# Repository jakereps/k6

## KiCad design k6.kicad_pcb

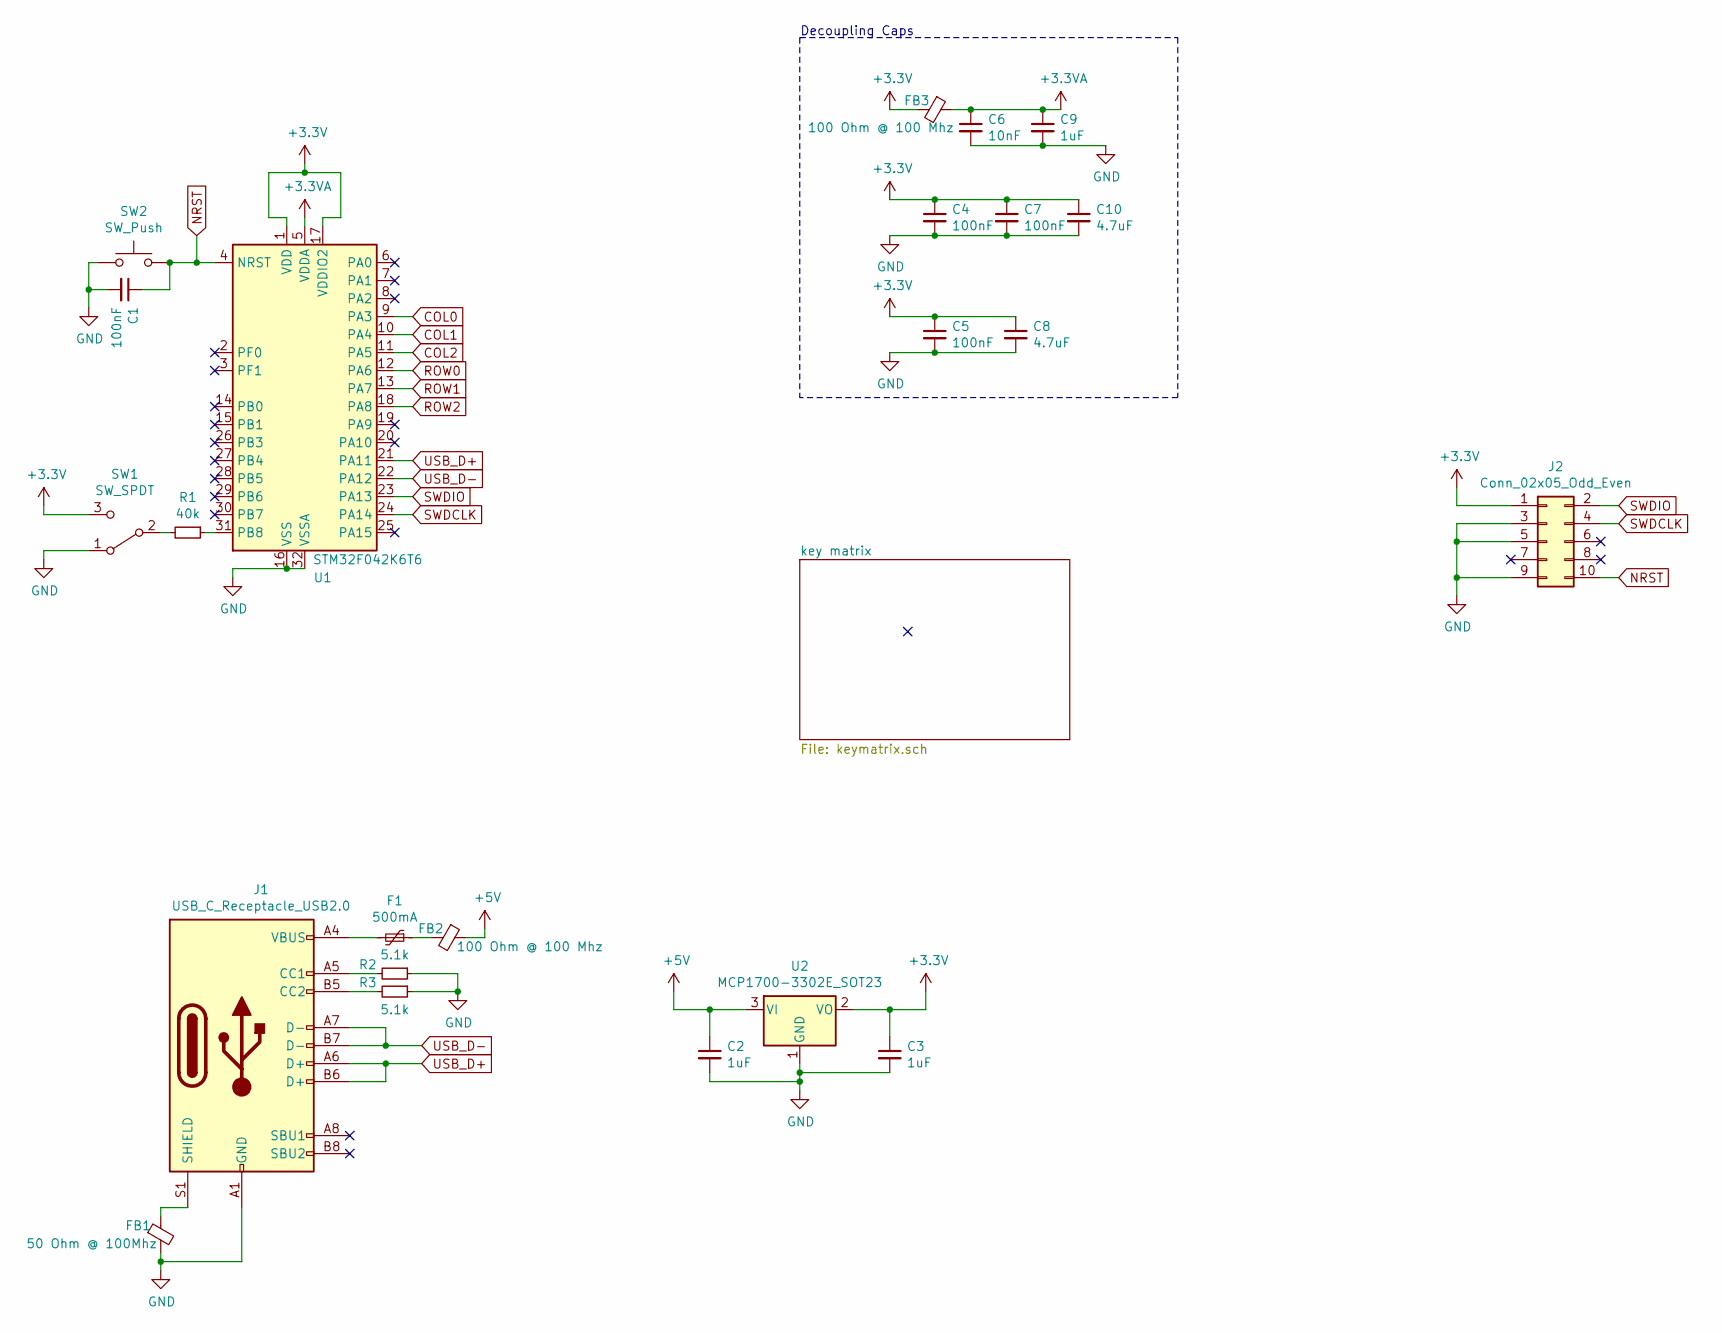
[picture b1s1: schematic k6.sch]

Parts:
C1, C4, C5, C7: 100nF; C_0805_2012Metric_Pad1.15x1.40mm_HandSolder
C2, C3, C9: 1uF; C_0805_2012Metric_Pad1.15x1.40mm_HandSolder
C6: 10nF; C_0805_2012Metric_Pad1.15x1.40mm_HandSolder
C8, C10: 4.7uF; C_0805_2012Metric_Pad1.15x1.40mm_HandSolder
F1: 500mA; Fuse_1206_3216Metric
FB1: 50 Ohm @ 100Mhz; L_0603_1608Metric_Pad1.05x0.95mm_HandSolder
FB2, FB3: 100 Ohm @ 100 Mhz; L_0603_1608Metric_Pad1.05x0.95mm_HandSolder
J1: USB_C_Receptacle_USB2.0; USB_C_Receptacle_HRO_TYPE-C-31-M-12
J2: Conn_02x05_Odd_Even; PinHeader_2x05_P2.00mm_Vertical
R1: 40k; R_0805_2012Metric_Pad1.15x1.40mm_HandSolder
R2, R3: 5.1k; R_0805_2012Metric_Pad1.15x1.40mm_HandSolder
SW1: SW_SPDT; SW_SPDT_CK-JS102011SAQN
SW2: SW_Push; SW_SPST_B3U-1000P
U1: STM32F042K6T6; LQFP-32_7x7mm_P0.8mm
U2: MCP1700-3302E_SOT23; SOT-23

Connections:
+3.3VA: C6.1, C9.1, FB3.1, U1.5 (VDDA)
+3V3: C3.1, C4.1, C5.1, C7.1, C8.1, C10.1, FB3.2, J2.1, SW1.3 (C), U1.1 (VDD), U1.17 (VDDIO2), U2.2 (VO)
+5V: C2.1, FB2.1, U2.3 (VI)
COL0: U1.9 (PA3); also elsewhere on the board
COL1: U1.10 (PA4); also elsewhere on the board
COL2: U1.11 (PA5); also elsewhere on the board
GND: C1.2, C2.2, C3.2, C4.2, C5.2, C6.2, C7.2, C8.2, C9.2, C10.2, FB1.2, J1.A1 (GND), J1.A12 (GND), J1.B1 (GND), J1.B12 (GND), J2.3, J2.5, J2.9, R2.1, R3.1, SW1.1 (A), SW2.1, U1.16 (VSS), U1.32 (VSSA), U2.1 (GND)
NRST: C1.1, J2.10, SW2.2, U1.4 (NRST)
unnamed: F1.1, FB2.2
unnamed: F1.2, J1.A4 (VBUS), J1.A9 (VBUS), J1.B4 (VBUS), J1.B9 (VBUS)
unnamed: FB1.1, J1.S1 (SHIELD)
unnamed: J1.A5 (CC1), R2.2
unnamed: J1.B5 (CC2), R3.2
unnamed: R1.1, U1.31 (PB8)
unnamed: R1.2, SW1.2 (B)
ROW0: U1.12 (PA6); also elsewhere on the board
ROW1: U1.13 (PA7); also elsewhere on the board
ROW2: U1.18 (PA8); also elsewhere on the board
SWDCLK: J2.4, U1.24 (PA14)
SWDIO: J2.2, U1.23 (PA13)
USB_D+: J1.A6 (D+), J1.B6 (D+), U1.21 (PA11)
USB_D-: J1.A7 (D-), J1.B7 (D-), U1.22 (PA12)

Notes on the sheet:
Decoupling Caps

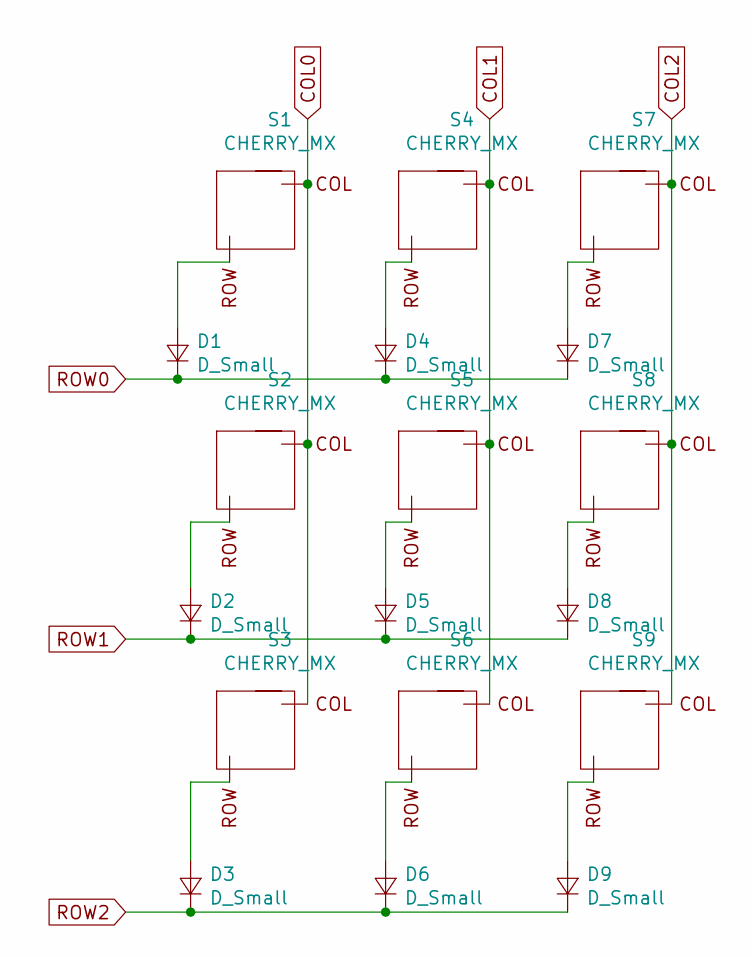
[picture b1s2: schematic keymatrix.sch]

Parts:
D1, D2, D3, D4, D5, D6, D7, D8, D9: D_Small; D_SOD-123
S1, S2, S3, S4, S5, S6, S7, S8, S9: CHERRY_MX; SW_Cherry_MX_1.00u_PCB

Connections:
COL0: S1.1 (S1), S2.1 (S1), S3.1 (S1); also elsewhere on the board
COL1: S4.1 (S1), S5.1 (S1), S6.1 (S1); also elsewhere on the board
COL2: S7.1 (S1), S8.1 (S1), S9.1 (S1); also elsewhere on the board
unnamed: D1.2 (A), S1.2 (S2)
unnamed: D2.2 (A), S2.2 (S2)
unnamed: D3.2 (A), S3.2 (S2)
unnamed: D4.2 (A), S4.2 (S2)
unnamed: D5.2 (A), S5.2 (S2)
unnamed: D6.2 (A), S6.2 (S2)
unnamed: D7.2 (A), S7.2 (S2)
unnamed: D8.2 (A), S8.2 (S2)
unnamed: D9.2 (A), S9.2 (S2)
ROW0: D1.1 (K), D4.1 (K), D7.1 (K); also elsewhere on the board
ROW1: D2.1 (K), D5.1 (K), D8.1 (K); also elsewhere on the board
ROW2: D3.1 (K), D6.1 (K), D9.1 (K); also elsewhere on the board

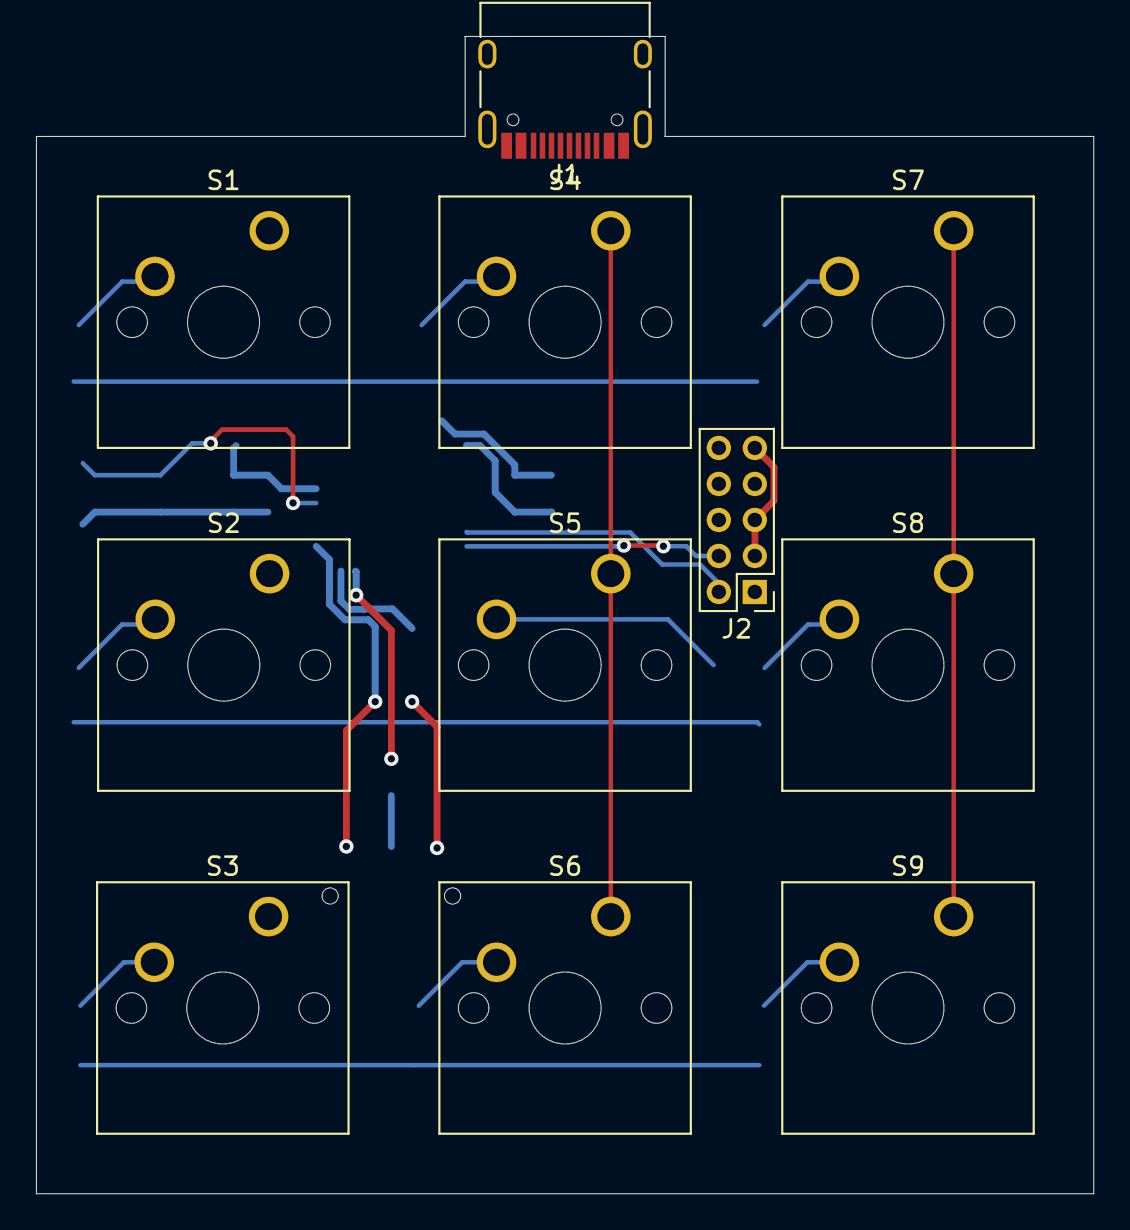
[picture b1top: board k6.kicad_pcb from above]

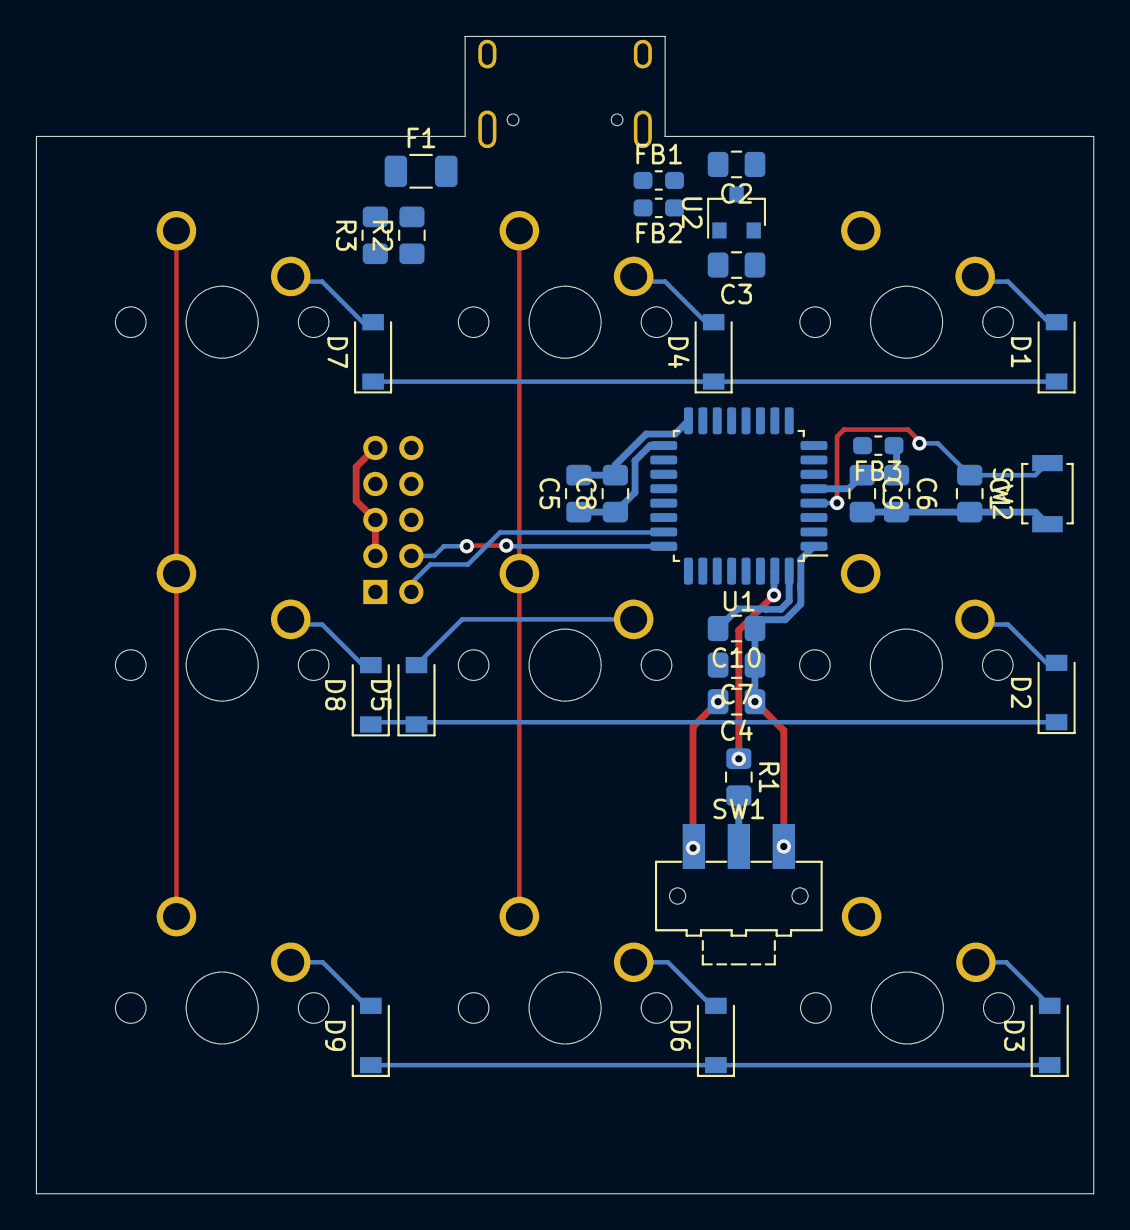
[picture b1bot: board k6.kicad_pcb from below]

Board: 2 copper layers, 58.7 x 64.3 mm, 41 parts (30 on the bottom side), 31 nets.

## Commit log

2020-05-23 Adding SWD pins
    Removed the start of the reset circuit and starting to add reset/debugging pins to program pcb (unsure if it will remain in the final but for protos will add).
2020-05-25 Start PCB Design
    Get barebones parts selected
2020-05-25 Move parts - part one
    No traces yet, only part movement
2020-05-25 Add some tracks - hate it
